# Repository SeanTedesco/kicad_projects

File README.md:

# kicad_projects
Small projects to become more familiar with PCB design and working with KiCad.

## STM-RF

## TRAFFIC LIGHT

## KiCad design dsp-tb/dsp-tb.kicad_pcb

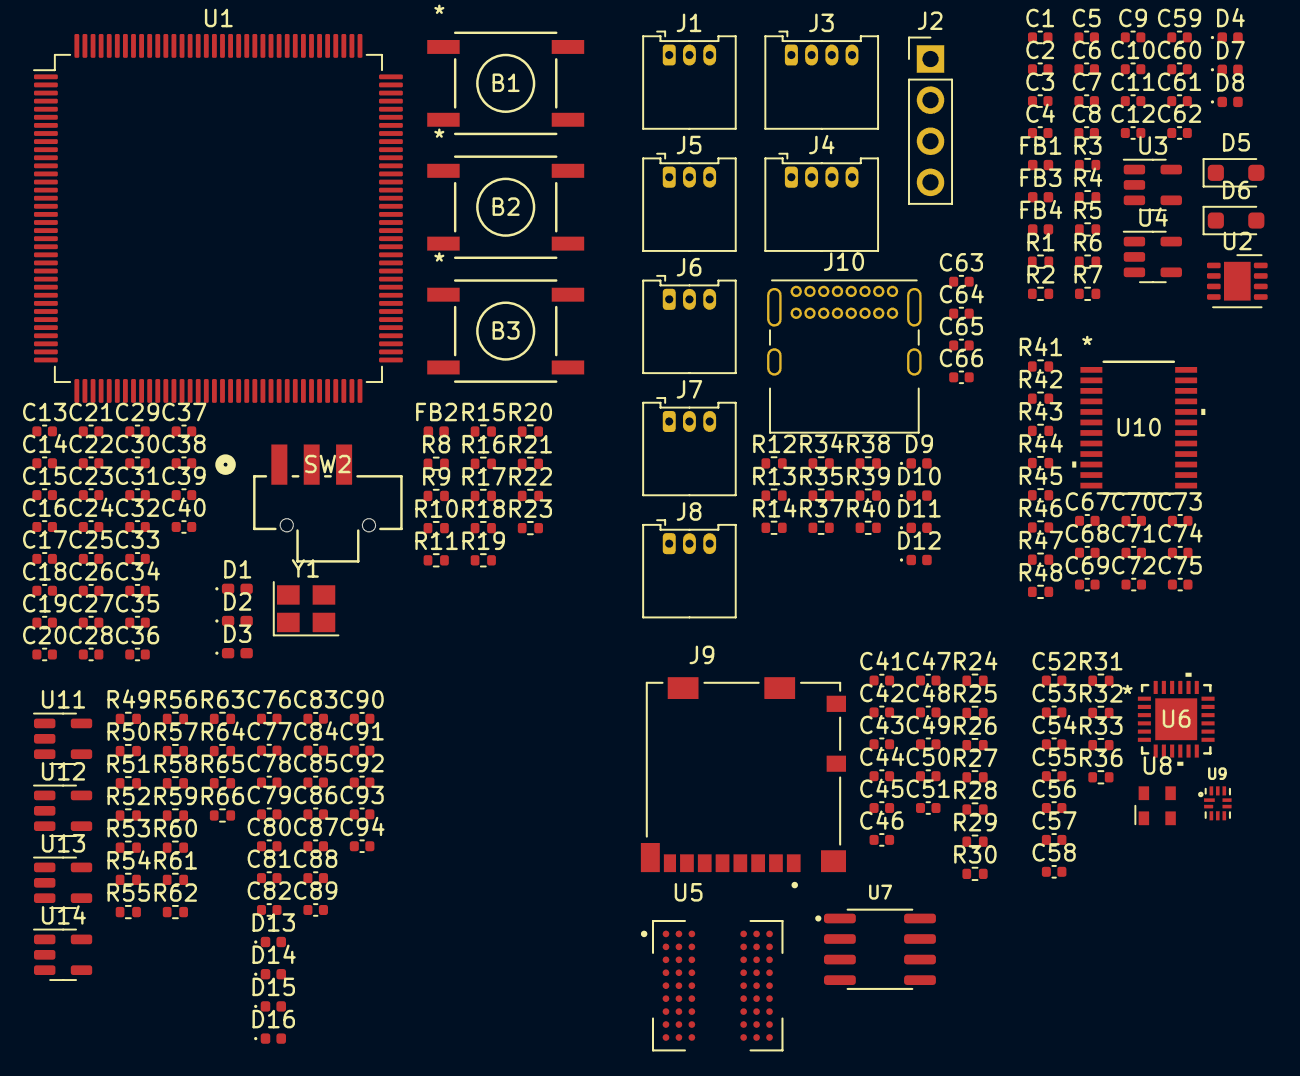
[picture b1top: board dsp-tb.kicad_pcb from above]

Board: 2 copper layers, 209 parts (0 on the bottom side), 168 nets, no tracks yet.

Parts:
B1, B2, B3: SW_MEC_5E; PTS645SL43SMTR92LFS_CNK
C1, C2, C3, C4, C5, C6, C7, C8, C13, C14, C32, C41, C45, C50, C51, C52, C53, C55, C68: 2u2; C_0402_1005Metric
C9, C10, C11, C12, C71, C72, C75, C86: 47u; C_0402_1005Metric
C15, C16, C17, C18, C19, C20, C21, C22, C23, C24, C25, C26, C27, C28, C29, C30, C31, C33, C34, C35, C36, C37, C38, C42, C43, C44, C46, C47, C48, C49, C54, C56, C57, C58, C59, C60, C61, C62, C67, C69, C70, C73, C74, C78, C83, C89, C93: 100n; C_0402_1005Metric
C39, C40, C63, C64, C65, C66: 10p; C_0402_1005Metric
C76, C79, C81, C84: 220p; C_0402_1005Metric
C77, C80, C82, C85, C87, C90, C91, C94: 10n; C_0402_1005Metric
C88, C92: 1n; C_0402_1005Metric
D1: RED; LED_0402_1005Metric_Pad0.77x0.64mm_HandSolder
D2: YLW; LED_0402_1005Metric_Pad0.77x0.64mm_HandSolder
D3: BLU; LED_0402_1005Metric_Pad0.77x0.64mm_HandSolder
D4, D7, D8, D9, D10, D11, D12, D13, D14, D15, D16: CG0402MLU-12G; D_0402_1005Metric
D5, D6: BAT165A; D_SOD-323_HandSoldering
FB1, FB3, FB4: 120R@100MHz; L_0402_1005Metric
FB2: 120R@100Mhz; L_0402_1005Metric
J1, J5, J6, J7, J8: Conn_01x03; Molex_PicoBlade_53048-0310_1x03_P1.25mm_Horizontal
J2: Conn_01x04; PinHeader_1x04_P2.54mm_Vertical
J3, J4: Conn_01x04; Molex_PicoBlade_53048-0410_1x04_P1.25mm_Horizontal
J9: 104031-0811; MOLEX_104031-0811
J10: USB_C_Receptacle_USB2.0; USB_C_Receptacle_GCT_USB4085
R1, R22: 0; R_0402_1005Metric
R2: DNP; R_0402_1005Metric
R3, R5, R24, R25, R26, R27, R28, R29, R30, R48: 47k; R_0402_1005Metric
R4: 15k; R_0402_1005Metric
R6: 91k; R_0402_1005Metric
R7: 10; R_0402_1005Metric
R8, R44, R45, R46, R47, R65, R66: 10k; R_0402_1005Metric
R9, R10, R11: 330; R_0402_1005Metric
R12, R13, R14, R17, R18, R19, R20, R21, R23, R31, R37, R38, R39, R40, R41: 33; R_0402_1005Metric
R15, R16: 4k7; R_0402_1005Metric
R32, R34, R35, R36: 5k1; R_0402_1005Metric
R33: 8k06; R_0402_1005Metric
R42, R43: 2k2; R_0402_1005Metric
R49, R53, R61, R64: 100R; R_0402_1005Metric
R50, R51, R54, R55, R59, R62: 1M; R_0402_1005Metric
R52, R56, R57, R58, R60, R63: 1k; R_0402_1005Metric
SW2: SW_SPDT; CSS-1210TB_NDC
U1: STM32H723ZGTx; LQFP-144_20x20mm_P0.5mm
U2: TLV76733QWDRBxQ1; VSON-8-1EP_3x3mm_P0.65mm_EP1.65x2.4mm
U3, U4: NCP718BSNADJT1G; SOT-23-5
U5: IS42S16800F-7BLI; BGA54C80P9X9_800X800X120
U6: USB3318C-CP-TR; QFN24_4X4MC_MCH
U7: IS25LP080D-JNLE; SOIC127P600X88-8N
U8: ECS-2520MV-130-BN-TR; Oscillator_SMD_Abracon_ASDMB-4Pin_2.5x2.0mm
U9: FSUSB42UMX; IC_FSUSB42UMX
U10: CS4270-CZZ; codec-cs4270
U11, U12, U13, U14: TLV9301xDBV; SOT-23-5
Y1: 403C11A24M; Crystal_SMD_3225-4Pin_3.2x2.5mm

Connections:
3V3_ADC: C61.1, D8.1 (K), FB4.1, J5.1, J6.1, J7.1, J8.1
+1V8: C6.1, C56.1, R5.1, U4.5 (OUT), U6.21 (VDD1.8)
+3.3VA: C34.1, C35.1, FB2.2, U1.32 (VREF+), U1.33 (VDDA)
+3V3: C2.1, C5.1, C15.1, C16.1, C17.1, C18.1, C19.1, C20.1, C21.1, C22.1, C23.1, C24.1, C25.1, C26.1, C27.1, C28.1, C29.1, C30.1, C31.1, C32.1, C33.1, C41.1, C42.1, C43.1, C44.1, C45.1, C46.1, C47.1, C48.1, C49.1, C50.1, C51.1, C52.1, C54.1, C57.1, C58.1, C62.1, C67.1, C68.1, C69.1, FB2.1, FB4.2, J9.4 (VDD), R1.1, R15.1, R16.1, R22.2, R24.1, R25.1, R26.1, R27.1, R28.1, R29.1, R30.1, R42.2, R43.2, SW2.3 (C), U1.6 (VBAT), U1.17 (VDD), U1.30 (VDD), U1.39 (VDD), U1.52 (VDD), U1.62 (VDD), U1.72 (VDD), U1.84 (VDD), U1.95 (VDD33USB), U1.108 (VDD), U1.121 (VDD), U1.131 (VDD), U1.144 (VDD), U2.1 (OUT), U4.1 (IN), U4.3 (EN), U5.A7 (VDDQ), U5.A9 (VDD), U5.B3 (VDDQ), U5.C7 (VDDQ), U5.D3 (VDDQ), U5.E7 (VDD), U5.J9 (VDD), U6.3 (VBAT), U6.17 (VDDIO), U7.8 (VCC), U8.1 (Standby), U8.4 (VDD), U9.9 (VCC), U10.5 (VD), U10.8 (VLC)
+5V: C4.1, R3.1, R7.1, U3.5 (OUT)
+5VA: C9.1, C10.1, C11.1, C12.1, C74.1, C75.1, C78.1, C83.1, C89.1, C93.1, R7.2, R57.1, U10.19 (VA), U11.5 (V+), U12.5 (V+), U13.5 (V+), U14.5 (V+)
/MCU/FMC_SDCLK: R23.1, U1.93 (PG8)
/MCU/MCU_BOOT0: R8.2, U1.138 (BOOT0)
/MCU/MCU_PDR_ON: R22.1, U1.143 (PDR_ON)
/MCU/QSPI_CLK_R: R21.1, U1.22 (PF10)
/MCU/SAI1_FS_A: R18.1, U1.3 (PE4)
/MCU/SAI1_MCLK_A: R17.1, U1.1 (PE2)
/MCU/SAI1_SCK_A: R19.1, U1.4 (PE5)
/MCU/SAI1_SD_A: R20.1, U1.5 (PE6)
ADC_IN14: C66.1, R40.1, U1.36 (PA2)
ADC_IN16: C65.1, R39.1, U1.34 (PA0)
ADC_IN17: C64.1, R38.1, U1.35 (PA1)
ADC_IN18: C63.1, R37.1, U1.40 (PA4)
AUDIO_IN_L: D13.1 (K), J3.1, R49.2
AUDIO_IN_R: D14.1 (K), J3.3, R53.2
AUDIO_OUT_L: C90.2, D15.1 (K), J4.1, R65.1
AUDIO_OUT_R: C94.2, D16.1 (K), J4.3, R66.1
CODEC_IN_L: C80.2, U10.15 (AINA)
CODEC_IN_R: C85.2, U10.16 (AINB)
CODEC_NRST: R47.2, U1.7 (PC13), U10.14 (*RST)
CODEC_OUT_L: C87.1, U10.22 (AOUTA)
CODEC_OUT_R: C91.1, U10.23 (AOUTB)
GND: B1.1, B1.2, B2.1, B2.2, B3.1, B3.2, C1.2, C2.2, C3.2, C4.2, C5.2, C6.2, C7.2, C8.2, C9.2, C10.2, C11.2, C12.2, C13.2, C14.2, C15.2, C16.2, C17.2, C18.2, C19.2, C20.2, C21.2, C22.2, C23.2, C24.2, C25.2, C26.2, C27.2, C28.2, C29.2, C30.2, C31.2, C32.2, C33.2, C34.2, C35.2, C36.1, C37.1, C38.1, C39.1, C40.1, C41.2, C42.2, C43.2, C44.2, C51.2, C52.2, C53.2, C54.2, C55.2, C56.2, C57.2, C58.2, C59.2, C60.2, C61.2, C62.2, C63.2, C64.2, C65.2, C66.2, C67.2, C68.2, C69.2, C70.2, C71.2, C72.2, C73.2, C74.2, C75.2, C76.2, C78.2, C79.2, C81.2, C83.2, C84.2, C86.2, C88.2, C89.2, C92.2, C93.2, D4.2 (A), D7.2 (A), D8.2 (A), D9.2 (A), D10.2 (A), D11.2 (A), D12.2 (A), D13.2 (A), D14.2 (A), D15.2 (A), D16.2 (A), J1.1, J1.2, J2.4, J3.2, J3.4, J4.2, J4.4, J5.3, J6.3, J7.3, J8.3, J9.6 (VSS), J9.G1 (GND), J9.G2 (GND), J9.G3 (GND), J9.G4 (GND), J10.A1 (GND), J10.A12 (GND), J10.B1 (GND), J10.B12 (GND), R2.2, R4.2, R6.2, R9.2, R10.2, R11.2, R33.2, R34.2, R35.2, R36.2, R44.1, R45.1, R46.1, R47.1, R48.1, R50.2, R54.2, R58.2, R65.2, R66.2, SW2.1 (A), U1.16 (VSS), U1.31 (VSSA), U1.38 (VSS), U1.51 (VSS), U1.61 (VSS), U1.83 (VSS), U1.94 (VSS), U1.107 (VSS), U1.120 (VSS), U1.130 (VSS), U2.4 (GND), U2.6 (GND), U2.9 (PAD), U3.2 (GND), U4.2 (GND), U5.A1 (VSS), U5.A3 (VSSQ), U5.B7 (VSSQ), U5.C3 (VSSQ), U5.D7 (VSSQ), U5.E3 (VSS), U5.J1 (VSS), U6.25 (EPAD), U7.4 (GND), U8.2 (GND), U9.3 (GND), U9.8 (~OE), U10.6 (DGND), U10.20 (AGND), U11.2 (V-), U12.2 (V-), U13.2 (V-), U14.2 (V-), Y1.2, Y1.4
I2C4_SCL: R43.1, U1.81 (PD12), U10.10 (M0)
I2C4_SDA: R42.1, U1.82 (PD13), U10.9 (M1)
I2S_BCLK: R19.2, U10.4 (SCLK)
I2S_DAC_IN: R20.2, U10.1 (SDIN)
I2S_MCLK: R17.2, U10.3 (MCLK)
I2S_WCLK: R18.2, U10.2 (LRCK)
MCU_BTN1: B3.3 (K), B3.4 (A), C37.2, R15.2
MCU_BTN2: B2.3 (K), B2.4 (A), C38.2, R16.2
MCU_SWCLK: R12.1, U1.109 (PA14(JTCK)
MCU_SWDIO: R13.1, U1.105 (PA13(JTMS)
MCU_SWO: R14.1, U1.133 (PB3(JTDO)
unnamed: B1.3 (K), B1.4 (A), C36.2, U1.25 (NRST)
unnamed: C13.1, U1.71 (VCAP)
unnamed: C14.1, U1.106 (VCAP)
unnamed: C45.2, C46.2, C47.2, C48.2
unnamed: C49.2, C50.2
unnamed: C76.1, C77.1, R49.1, R50.1
unnamed: C79.1, C80.1, R52.1
unnamed: C81.1, C82.1, R53.1, R54.1
unnamed: C84.1, C85.1, R56.1
unnamed: C87.2, R59.2, R60.2
unnamed: C90.1, R61.1
unnamed: C91.2, R62.2, R63.2
unnamed: C94.1, R64.1
unnamed: D1.1 (K), R9.1
unnamed: D2.1 (K), R10.1
unnamed: D3.1 (K), R11.1
unnamed: C7.1, D5.1 (K), FB1.1
unnamed: C60.1, D6.2 (A), FB3.2
unnamed: C1.1, C3.1, C8.1, D6.1 (K), FB1.2, U2.5 (EN), U2.8 (IN), U3.1 (IN), U3.3 (EN)
unnamed: D9.1 (K), J5.2, R37.2
unnamed: D10.1 (K), J6.2, R38.2
unnamed: D11.1 (K), J7.2, R39.2
unnamed: D12.1 (K), J8.2, R40.2
unnamed: J2.1, R12.2
unnamed: J2.2, R13.2
unnamed: J2.3, R14.2
unnamed: J10.A5 (CC1), R35.1
unnamed: J10.B5 (CC2), R34.1
unnamed: R8.1, SW2.2 (B)
unnamed: C39.2, U1.23 (PH0), Y1.1
unnamed: C40.2, U1.24 (PH1), Y1.3
unnamed: R1.2, R2.1, U2.3 (SNS)
unnamed: R3.2, R4.1, U3.4 (ADJ)
unnamed: R5.2, R6.1, U4.4 (ADJ)
unnamed: R33.1, U6.24 (RBIAS)
unnamed: R31.1, U6.23 (REFCLK)
unnamed: R32.2, U6.2 (VBUS)
unnamed: C55.1, U6.4 (VDD3.3)
unnamed: R31.2, U8.3 (Out)
unnamed: C72.1, C73.1, U10.18 (FILT+)
unnamed: R44.2, U10.11 (I2S/*LJ)
unnamed: R45.2, U10.12 (MDIV1)
unnamed: R46.2, U10.13 (MDIV2)
unnamed: R41.1, R48.2, U10.7 (SDOUT)
unnamed: C70.1, C71.1, U10.17 (VQ)
unnamed: C77.2, R51.2, U11.3 (+)
unnamed: R52.2, U11.1, U11.4 (-)
unnamed: C82.2, R55.2, U12.3 (+)
unnamed: R56.2, U12.1, U12.4 (-)
unnamed: C88.1, R60.1, U13.3 (+)
unnamed: R61.2, U13.1, U13.4 (-)
unnamed: C92.1, R63.1, U14.3 (+)
unnamed: R64.2, U14.1, U14.4 (-)
QSPI_CLK: R21.2, U7.6 (SCK)
QSPI_IO0: U1.20 (PF8), U7.2 (SO(IO1))
QSPI_IO1: U1.21 (PF9), U7.5 (SI(IO0))
QSPI_IO2: U1.19 (PF7), U7.3 (WP#(IO2))
QSPI_IO3: U1.18 (PF6), U7.7 (HOLD/RESET)
QSPI_NCS: R30.2, U1.91 (PG6), U7.1 (CE#)
RAM_A0: U1.10 (PF0), U5.H7 (A0)
RAM_A1: U1.11 (PF1), U5.H8 (A1)
RAM_A2: U1.12 (PF2), U5.J8 (A2)
RAM_A3: U1.13 (PF3), U5.J7 (A3)
RAM_A4: U1.14 (PF4), U5.J3 (A4)
RAM_A5: U1.15 (PF5), U5.J2 (A5)
RAM_A6: U1.50 (PF12), U5.H3 (A6)
RAM_A7: U1.53 (PF13), U5.H2 (A7)
RAM_A8: U1.54 (PF14), U5.H1 (A8)
RAM_A9: U1.55 (PF15), U5.G3 (A9)
RAM_A10: U1.56 (PG0), U5.H9 (A10)
RAM_A11: U1.57 (PG1), U5.G2 (A11)
RAM_BA0: U1.89 (PG4), U5.G7 (BA0)
RAM_BA1: U1.90 (PG5), U5.G8 (BA1)
RAM_CKE: U1.45 (PC5), U5.F3 (CKE)
RAM_CLK: R23.2, U5.F2 (CLK)
RAM_D0: U1.85 (PD14), U5.A8 (DQ0)
RAM_D1: U1.86 (PD15), U5.B9 (DQ1)
RAM_D2: U1.114 (PD0), U5.B8 (DQ2)
RAM_D3: U1.115 (PD1), U5.C9 (DQ3)
RAM_D4: U1.58 (PE7), U5.C8 (DQ4)
RAM_D5: U1.59 (PE8), U5.D9 (DQ5)
RAM_D6: U1.60 (PE9), U5.D8 (DQ6)
RAM_D7: U1.63 (PE10), U5.E9 (DQ7)
RAM_D8: U1.64 (PE11), U5.E1 (DQ8)
RAM_D9: U1.65 (PE12), U5.D2 (DQ9)
RAM_D10: U1.66 (PE13), U5.D1 (DQ10)
RAM_D11: U1.67 (PE14), U5.C2 (DQ11)
RAM_D12: U1.68 (PE15), U5.C1 (DQ12)
RAM_D13: U1.77 (PD8), U5.B2 (DQ13)
RAM_D14: U1.78 (PD9), U5.B1 (DQ14)
RAM_D15: U1.79 (PD10), U5.A2 (DQ15)
RAM_DMH: U1.142 (PE1), U5.F1 (DQMH)
RAM_DML: U1.141 (PE0), U5.E8 (DQML)
RAM_NCAS: U1.132 (PG15), U5.F7 (*CAS)
RAM_NCS: U1.44 (PC4), U5.G9 (*CS)
RAM_NRAS: U1.49 (PF11), U5.F8 (*RAS)
RAM_NWE: U1.43 (PA7), U5.F9 (*WE)
SAI1_SD_B: R41.2, U1.2 (PE3)
SD_CLK: J9.5 (CLK), U1.122 (PD6)
SD_CMD: J9.3 (CMD), R29.2, U1.123 (PD7)
SD_D0: J9.7 (DAT0), R24.2, U1.124 (PG9)
SD_D1: J9.8 (DAT1), R25.2, U1.125 (PG10)
SD_D2: J9.1 (DAT2), R26.2, U1.126 (PG11)
SD_D3: J9.2 (CD/DAT3), R27.2, U1.127 (PG12)
SD_DET: J9.9 (SW-1), R28.2, U1.128 (PG13)
ULPI_CLK: U1.41 (PA5), U6.12 (CLKOUT)
ULPI_D0: U1.37 (PA3), U6.16 (DATA0)
ULPI_D1: U1.46 (PB0), U6.15 (DATA1)
ULPI_D2: U1.47 (PB1), U6.14 (DATA2)
ULPI_D3: U1.69 (PB10), U6.13 (DATA3)
ULPI_D4: U1.70 (PB11), U6.11 (DATA4)
ULPI_D5: U1.73 (PB12), U6.10 (DATA5)
ULPI_D6: U1.74 (PB13), U6.9 (DATA6)
ULPI_D7: U1.135 (PB5), U6.8 (DATA7)
ULPI_DIR: U1.28 (PC2_C), U6.19 (DIR)
ULPI_NXT: U1.29 (PC3_C), U6.18 (NXT)
ULPI_STP: U1.26 (PC0), U6.20 (STP)
USB_D_N: J10.A7 (D-), J10.B7 (D-), U9.2 (D-)
USB_D_P: J10.A6 (D+), J10.B6 (D+), U9.1 (D+)
USB_FS_D_N: U1.103 (PA11), U9.6 (HSD2-)
USB_FS_D_P: U1.104 (PA12), U9.7 (HSD2+)
USB_HS_D_N: U6.5 (DM), U9.4 (HSD1-)
USB_HS_D_P: U6.6 (DP), U9.5 (HSD1+)
USB_NRST: U1.129 (PG14), U6.22 (RESETB)
USB_SW: R36.1, U1.102 (PA10), U9.10 (SEL)
VBUS: C59.1, D7.1 (K), FB3.1, J10.A4 (VBUS), J10.A9 (VBUS), J10.B4 (VBUS), J10.B9 (VBUS)
VCC: D4.1 (K), D5.2 (A), J1.3
VCOM: C86.1, R51.1, R55.1, R57.2, R58.1, R59.1, R62.1
VUSB_FILT: C53.1, R32.1

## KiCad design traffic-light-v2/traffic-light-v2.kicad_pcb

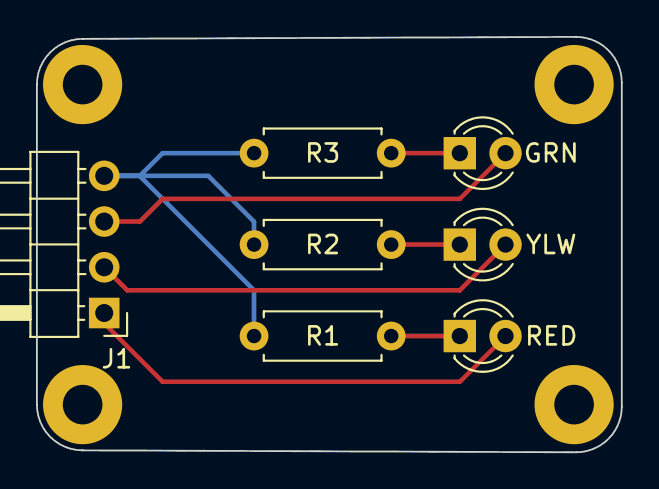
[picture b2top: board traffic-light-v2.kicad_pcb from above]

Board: 2 copper layers, 32.5 x 23.1 mm, 11 parts (0 on the bottom side), 7 nets.

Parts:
GRN: GRN; LED_D3.0mm
H1, H2, H3, H4: MountingHole; MountingHole_2.2mm_M2_Pad
J1: Conn_01x04; PinHeader_1x04_P2.54mm_Horizontal
R1, R2, R3: 330; R_Axial_DIN0207_L6.3mm_D2.5mm_P7.62mm_Horizontal
RED: RED; LED_D3.0mm
YLW: YLW; LED_D3.0mm

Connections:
GND: J1.4, R1.2, R2.2, R3.2
LED_GRN: GRN.2 (A), J1.3
LED_RED: J1.1, RED.2 (A)
LED_YLW: J1.2, YLW.2 (A)
unnamed: R1.1, RED.1 (K)
unnamed: R2.1, YLW.1 (K)
unnamed: GRN.1 (K), R3.1

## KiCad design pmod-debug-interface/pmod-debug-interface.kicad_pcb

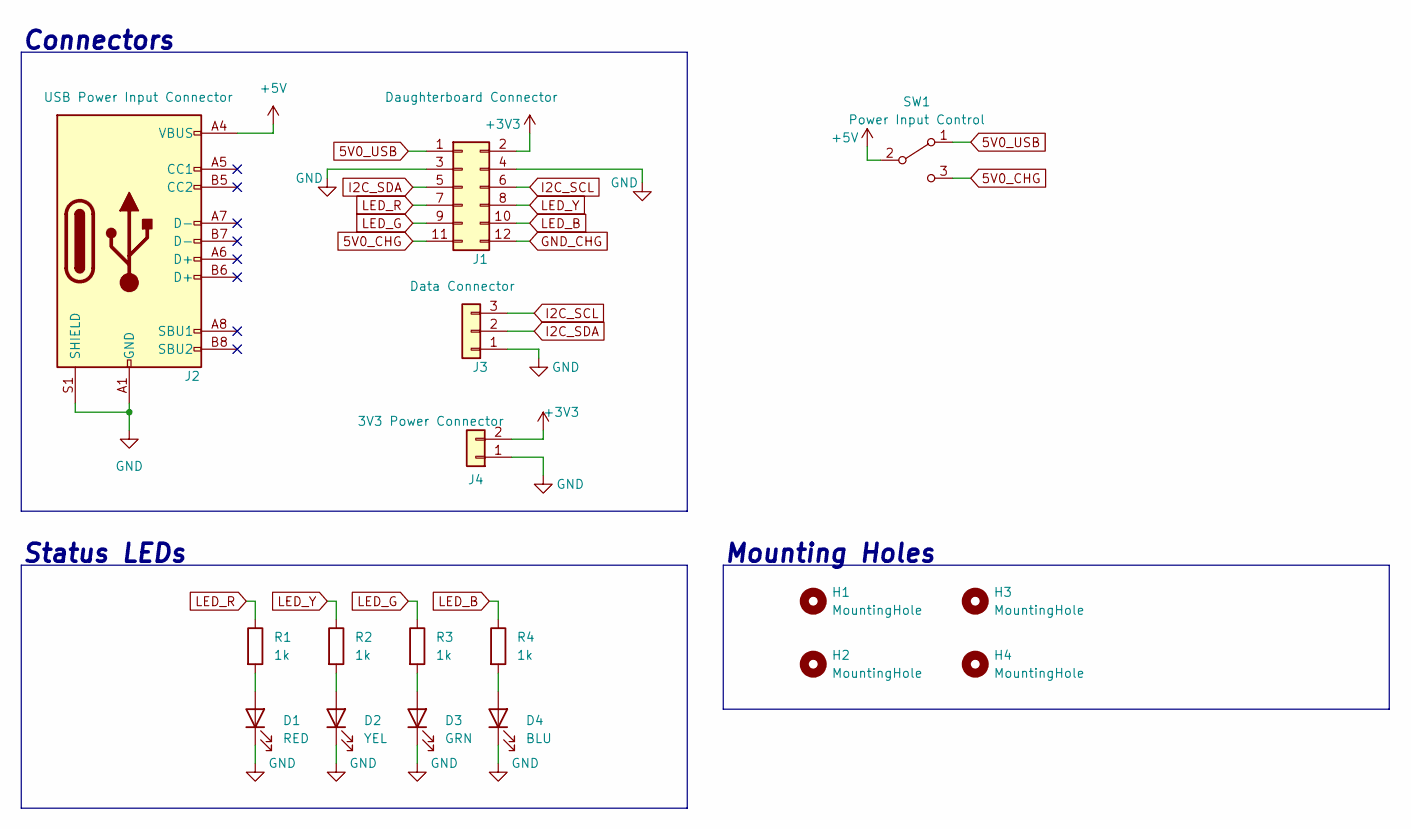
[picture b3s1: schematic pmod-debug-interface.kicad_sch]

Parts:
D1: RED; LED_D3.0mm
D2: YEL; LED_D3.0mm
D3: GRN; LED_D3.0mm
D4: BLU; LED_D3.0mm
H1, H2, H3, H4: MountingHole; MountingHole_2.2mm_M2_Pad
J1: Daughterboard Connector; PinHeader_2x06_P2.54mm_Horizontal
J2: USB Power Input Connector; USB_C_Receptacle_GCT_USB4085
J3: Data Connector; PinHeader_1x03_P2.54mm_Vertical
J4: 3V3 Power Connector; PinSocket_1x02_P2.54mm_Vertical
R1, R2, R3, R4: 1k; R_Axial_DIN0207_L6.3mm_D2.5mm_P7.62mm_Horizontal
SW1: Power Input Control; L102021MS02Q

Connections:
5V0_CHG: J1.11, SW1.3 (C)
5V0_USB: J1.1, SW1.1 (A)
+3V3: J1.2, J4.2
+5V: J2.A4 (VBUS), J2.A9 (VBUS), J2.B4 (VBUS), J2.B9 (VBUS), SW1.2 (B)
GND: D1.1 (K), D2.1 (K), D3.1 (K), D4.1 (K), J1.3, J1.4, J2.A1 (GND), J2.A12 (GND), J2.B1 (GND), J2.B12 (GND), J2.S1 (SHIELD), J3.1, J4.1
GND_CHG: J1.12
I2C_SCL: J1.6, J3.3
I2C_SDA: J1.5, J3.2
LED_B: J1.10, R4.1
LED_G: J1.9, R3.1
LED_R: J1.7, R1.1
LED_Y: J1.8, R2.1
unnamed: D1.2 (A), R1.2
unnamed: D2.2 (A), R2.2
unnamed: D3.2 (A), R3.2
unnamed: D4.2 (A), R4.2

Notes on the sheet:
Connectors
Mounting Holes
Status LEDs

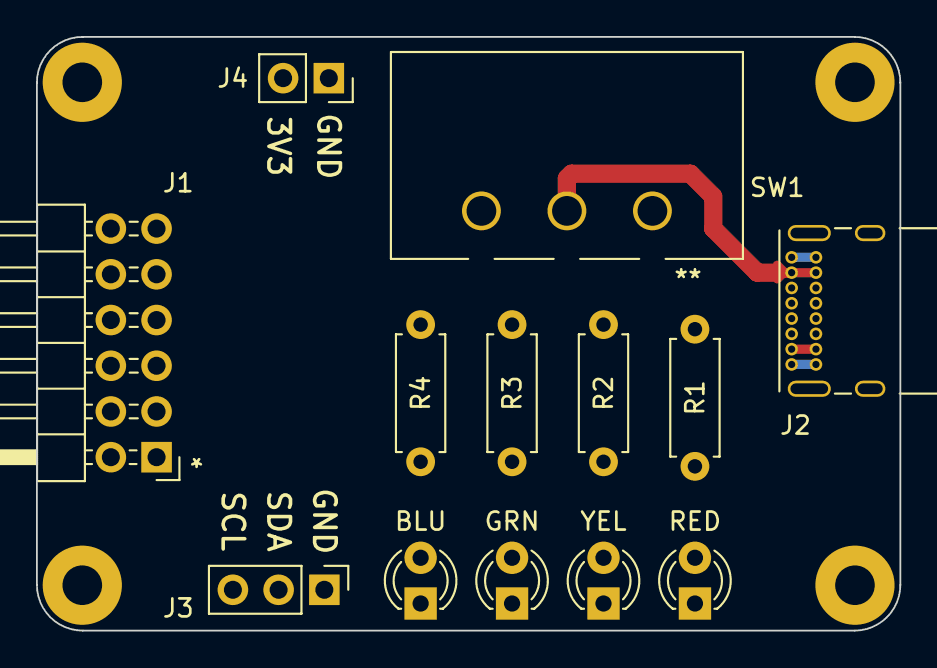
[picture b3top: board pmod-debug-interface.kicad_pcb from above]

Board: 2 copper layers, 48.0 x 33.0 mm, 17 parts (0 on the bottom side), 15 nets.

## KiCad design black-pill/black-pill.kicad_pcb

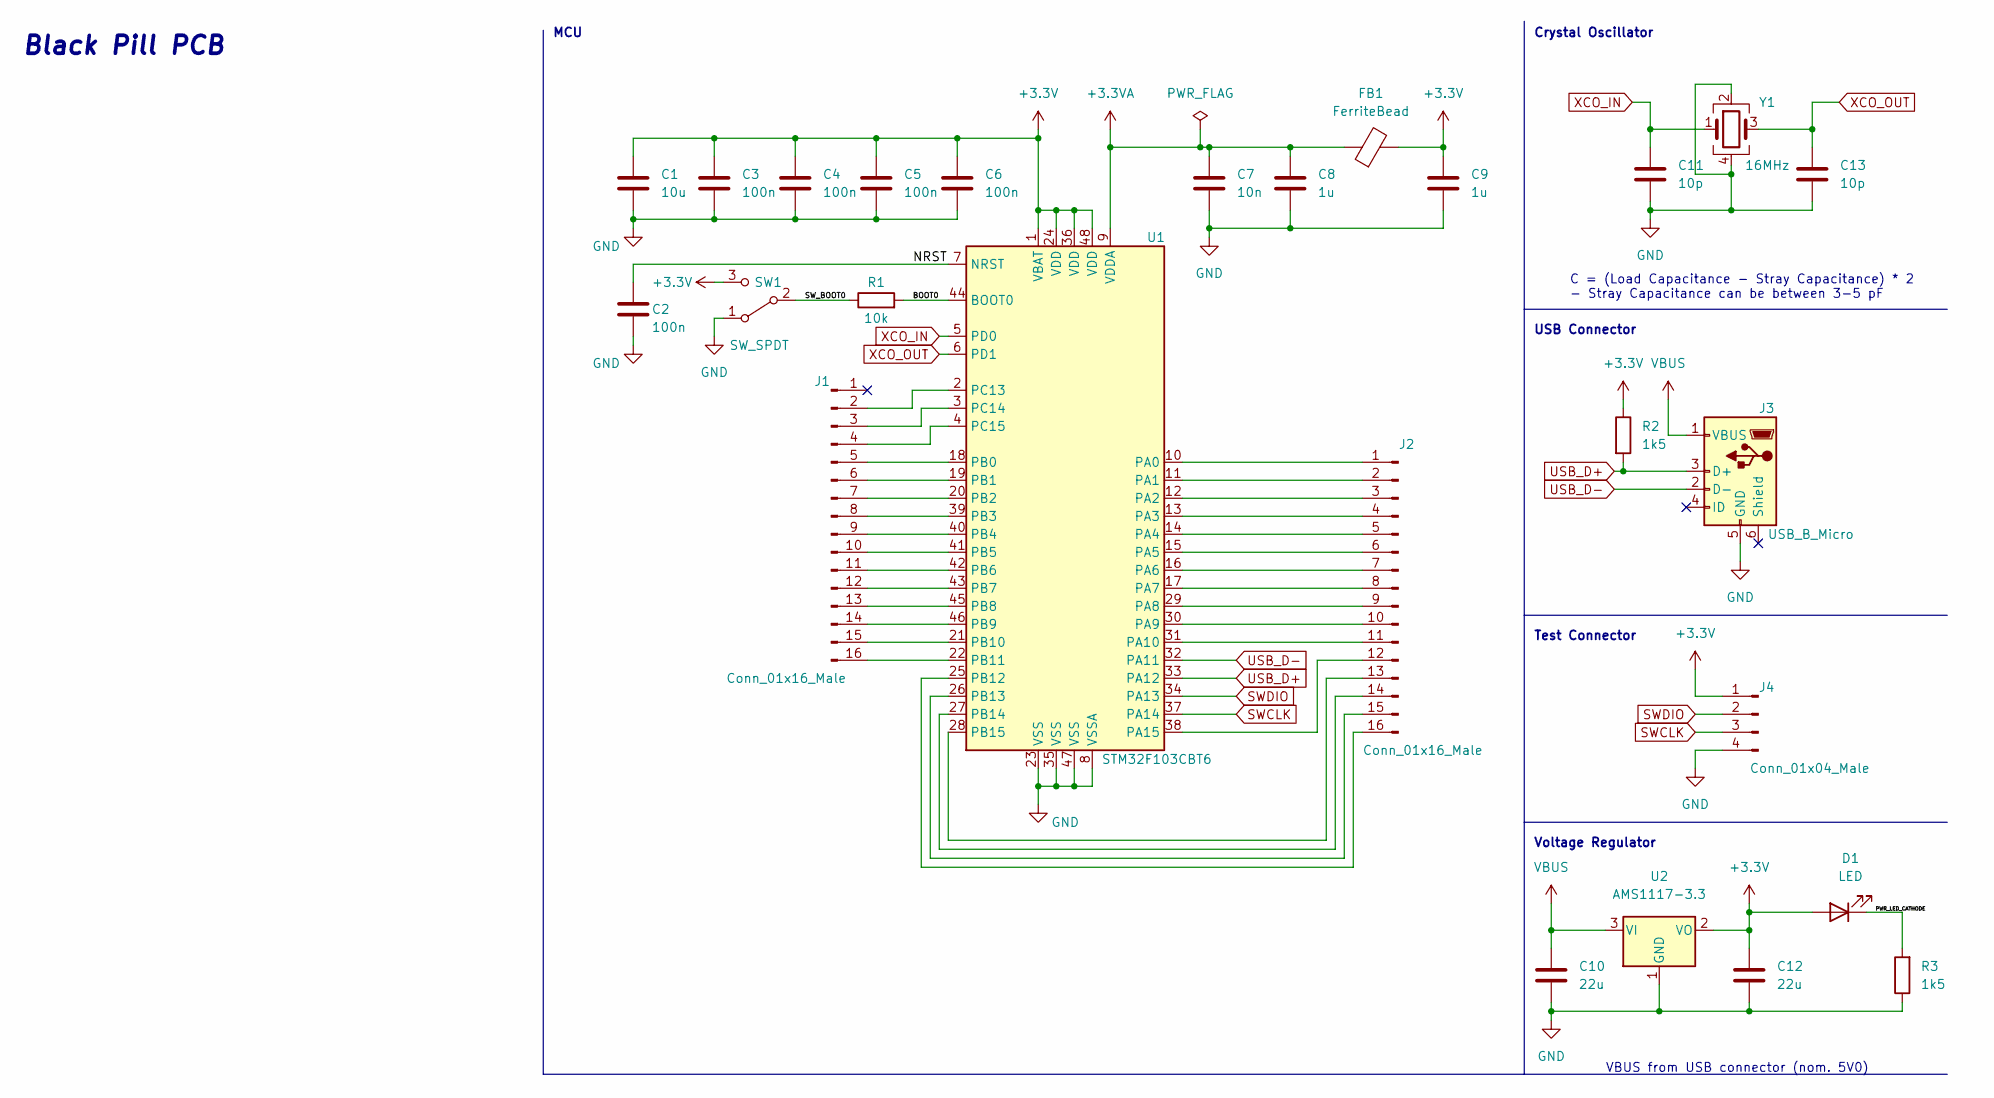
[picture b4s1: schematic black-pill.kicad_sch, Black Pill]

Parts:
C1: 10u; C_0603_1608Metric
C2, C3, C4, C5, C6: 100n; C_0402_1005Metric
C7: 10n; C_0402_1005Metric
C8, C9: 1u; C_0402_1005Metric
C10, C12: 22u; C_0805_2012Metric
C11, C13: 10p; C_0402_1005Metric
D1: LED; LED_0603_1608Metric
FB1: FerriteBead; L_0603_1608Metric
J1, J2: Conn_01x16_Male; PinHeader_1x16_P2.54mm_Vertical
J3: USB_B_Micro; USB_Micro-B_Wuerth_629105150521
J4: Conn_01x04_Male; PinHeader_1x04_P2.54mm_Vertical
R1: 10k; R_0402_1005Metric
R2, R3: 1k5; R_0402_1005Metric
SW1: SW_SPDT; SW_SPDT_PCM12
U1: STM32F103CBT6; LQFP-48_7x7mm_P0.5mm
U2: AMS1117-3.3; SOT-223-3_TabPin2
Y1: 16MHz; Crystal_SMD_3225-4Pin_3.2x2.5mm

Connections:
+3.3V: C1.1, C3.1, C4.1, C5.1, C6.1, C9.1, C12.1, D1.2 (A), FB1.2, J4.1, R2.1, SW1.3 (C), U1.1 (VBAT), U1.24 (VDD), U1.36 (VDD), U1.48 (VDD), U2.2 (VO)
+3.3VA: C7.1, C8.1, FB1.1, U1.9 (VDDA)
/BOOT0: R1.2, U1.44 (BOOT0)
/NRST: C2.1, U1.7 (NRST)
/PWR_LED_CATHODE: D1.1 (K), R3.2
/SW_BOOT0: R1.1, SW1.2 (B)
GND: C1.2, C2.2, C3.2, C4.2, C5.2, C6.2, C7.2, C8.2, C9.2, C10.2, C11.2, C12.2, C13.2, J3.5 (GND), J4.4, R3.1, SW1.1 (A), U1.8 (VSSA), U1.23 (VSS), U1.35 (VSS), U1.47 (VSS), U2.1 (GND), Y1.2, Y1.4
unnamed: J1.2, U1.2 (PC13)
unnamed: J1.3, U1.3 (PC14)
unnamed: J1.4, U1.4 (PC15)
unnamed: J1.5, U1.18 (PB0)
unnamed: J1.6, U1.19 (PB1)
unnamed: J1.7, U1.20 (PB2)
unnamed: J1.8, U1.39 (PB3)
unnamed: J1.9, U1.40 (PB4)
unnamed: J1.10, U1.41 (PB5)
unnamed: J1.11, U1.42 (PB6)
unnamed: J1.12, U1.43 (PB7)
unnamed: J1.13, U1.45 (PB8)
unnamed: J1.14, U1.46 (PB9)
unnamed: J1.15, U1.21 (PB10)
unnamed: J1.16, U1.22 (PB11)
unnamed: J2.1, U1.10 (PA0)
unnamed: J2.2, U1.11 (PA1)
unnamed: J2.3, U1.12 (PA2)
unnamed: J2.4, U1.13 (PA3)
unnamed: J2.5, U1.14 (PA4)
unnamed: J2.6, U1.15 (PA5)
unnamed: J2.7, U1.16 (PA6)
unnamed: J2.8, U1.17 (PA7)
unnamed: J2.9, U1.29 (PA8)
unnamed: J2.10, U1.30 (PA9)
unnamed: J2.11, U1.31 (PA10)
unnamed: J2.12, U1.38 (PA15)
unnamed: J2.13, U1.28 (PB15)
unnamed: J2.14, U1.27 (PB14)
unnamed: J2.15, U1.26 (PB13)
unnamed: J2.16, U1.25 (PB12)
SWCLK: J4.3, U1.37 (PA14)
SWDIO: J4.2, U1.34 (PA13)
USB_D+: J3.3 (D+), R2.2, U1.33 (PA12)
USB_D-: J3.2 (D-), U1.32 (PA11)
VBUS: C10.1, J3.1 (VBUS), U2.3 (VI)
XCO_IN: C11.1, U1.5 (PD0), Y1.1
XCO_OUT: C13.1, U1.6 (PD1), Y1.3

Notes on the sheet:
Test Connector
Crystal Oscillator
MCU
USB Connector
Voltage Regulator
C = (Load Capacitance - Stray Capacitance) * 2 - Stray Capacitance can be between 3-5 pF
VBUS from USB connector (nom. 5V0)
Black Pill PCB

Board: 2 copper layers, 26 parts (0 on the bottom side), 45 nets, no tracks yet.

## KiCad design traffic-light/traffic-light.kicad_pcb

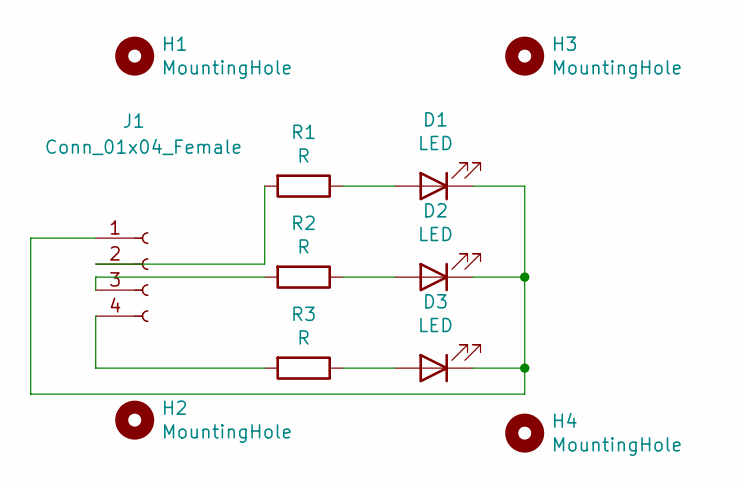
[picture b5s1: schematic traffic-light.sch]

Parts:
D1, D2, D3: LED; LED_D3.0mm
H1, H2, H3, H4: MountingHole; MountingHole_2.5mm_Pad
J1: Conn_01x04_Female; PinHeader_1x04_P2.54mm_Horizontal
R1, R2, R3: R; R_Axial_DIN0204_L3.6mm_D1.6mm_P5.08mm_Horizontal

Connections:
unnamed: D1.1 (K), D2.1 (K), D3.1 (K), J1.1
unnamed: D1.2 (A), R1.1
unnamed: D2.2 (A), R2.1
unnamed: D3.2 (A), R3.1
unnamed: J1.2, R1.2
unnamed: J1.3, R2.2
unnamed: J1.4, R3.2

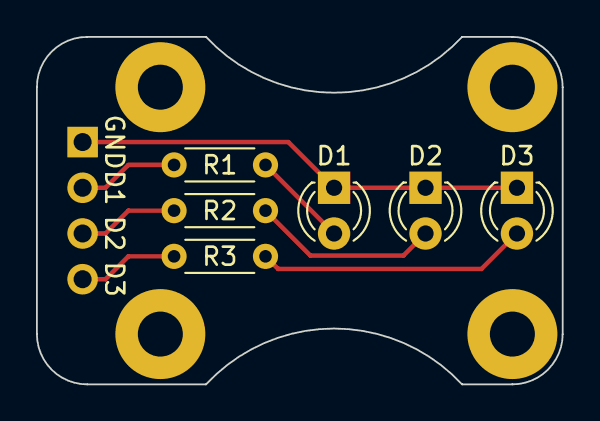
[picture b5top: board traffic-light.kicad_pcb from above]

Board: 2 copper layers, 29.2 x 19.3 mm, 11 parts (1 on the bottom side), 7 nets.

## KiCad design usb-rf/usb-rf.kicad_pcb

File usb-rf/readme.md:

# RF-USB - Universal Receiver

# Components

## STM32L432KB
- include USB interface within the chip
- ultra low power (minimal processing is required, just need an interface
 between USB and RF radio. 

## RF24L01
- 2.4 GHz Transceiver
- low cost 
- has been seen in many Arduino projects, so can use some existing librar
ies.
- SMA connector used as to not limit the antenna selection, and reducing
form factor of PCB. 

# PCB Design 

## Layers
The RF-USB uses a 4-layer PCB broken down per the following: 
- 1st Layer: Signals
- 2nd Layer: Ground
- 3rd Layer: Power (3V3)
- 4th Layer: Signal

## Design Guidelines
1. De-coupling capacitors will be placed as close to each device as possible. 
1. ESD protection device shall be as close to the USB port as possible.
1. Each ground and power pad shall have a via.

# Documentation

[nRF24L01 Datasheet](https://www.mouser.com/datasheet/2/297/nRF24L01_Product_Specification_v2_0-9199.pdf)

[STM32L432KB Datatsheet](https://www.st.com/resource/en/datasheet/stm32l432kc.pdf)

[STM32L4 Series Hardware Development](https://www.st.com/resource/en/application_note/dm00125306-getting-started-with-stm32l4-series-and-stm32l4-series-hardware-development-stmicroelectronics.pdf)

[JCLPCB Design Capabilities](https://jlcpcb.com/capabilities/Capabilities)

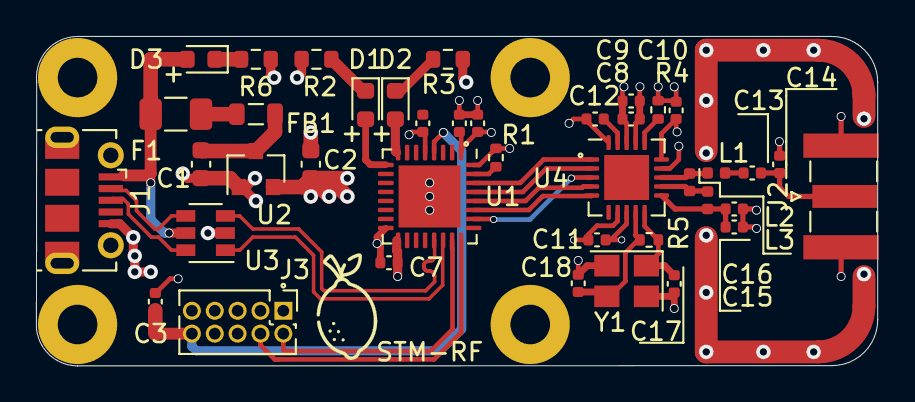
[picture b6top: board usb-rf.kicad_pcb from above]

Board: 4 copper layers, 46.7 x 18.3 mm, 44 parts (0 on the bottom side), 33 nets.

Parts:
C1, C2: 10u; C_0603_1608Metric
C3, C5, C6, C7: 100n; C_0402_1005Metric
C4: 1u; C_0402_1005Metric
C8: 10u; C_0402_1005Metric
C9, C10, C11: 10n; C_0402_1005Metric
C12: 33n; C_0402_1005Metric
C13: 1p5; C_0402_1005Metric
C14: 1p; C_0402_1005Metric
C15: 2n2; C_0402_1005Metric
C16: 4p7; C_0402_1005Metric
C17, C18: 12p; C_0402_1005Metric
D1: GR; LED_0603_1608Metric
D2: YL; LED_0603_1608Metric
D3: RD; LED_0603_1608Metric
F1: 100mA; Fuse_1206_3216Metric
FB1: 100 @ 100MHz; L_0805_2012Metric
H1, H2, H3, H4: MountingHole; MountingHole_2.2mm_M2_Pad
J1: USB_B_Micro; USB_Micro-B_Molex-105017-0001-SeanCopy
J2: SMA; SMA_Samtec_SMA-J-P-X-ST-EM1_EdgeMount-SeanCopyy
J3: ARM 10 pin; PinHeader_2x05_P1.27mm_Vertical
L1: 3n9; L_0402_1005Metric
L2: 8n2; L_0402_1005Metric
L3: 2n7; L_0402_1005Metric
R1: 10k; R_0402_1005Metric
R2, R3, R6: 2k2; R_0603_1608Metric
R4: 22k; R_0402_1005Metric
R5: 1M; R_0402_1005Metric
U1: STM32L432KBUx; QFN-32-1EP_5x5mm_P0.5mm_EP3.45x3.45mm
U2: XC6206PxxxMR; SOT-23
U3: USBLC6-2SC6; SOT-23-6
U4: nRF24L01P; QFN-20-1EP_4x4mm_P0.5mm_EP2.5x2.5mm
Y1: 16 MHz; Crystal_SMD_3225-4Pin_3.2x2.5mm

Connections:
+3V3: C2.1, C4.1, C5.1, C6.1, C7.1, C8.1, C9.1, C10.1, C11.1, J3.1, U1.1, U1.5, U1.17, U2.2, U4.7, U4.15, U4.18
+5V: D3.2, F1.1, J1.1, U3.5
GND: C1.2, C2.2, C3.2, C4.2, C5.2, C6.2, C7.2, C8.2, C9.2, C10.2, C11.2, C12.2, C14.1, C15.1, C16.1, C17.1, C18.1, J1.5, J2.2, J3.3, J3.5, J3.9, R1.2, R2.2, R3.2, R4.2, R6.1, U1.16, U1.32, U1.33, U2.1, U3.2, U4.8, U4.14, U4.17, U4.20, Y1.2, Y1.4
NRF_ANT1: L2.2, L3.1, U4.12
NRF_ANT2: L1.1, L2.1, U4.13
NRF_CE: U1.30, U4.1
NRF_IRQ: U1.25, U4.6
NRF_VDD_PA: C15.2, C16.2, L3.2, U4.11
NRF_XC1: C17.2, R5.1, U4.10, Y1.1
NRF_XC2: C18.2, R5.2, U4.9, Y1.3
NRST: C3.1, J3.10, U1.4
unnamed: C1.1, FB1.1, U2.3
unnamed: C12.1, U4.19
unnamed: C13.1, C14.2, J2.1
unnamed: C13.2, L1.2
unnamed: D1.1, R2.1
unnamed: D1.2, U1.9
unnamed: D2.1, R3.1
unnamed: D2.2, U1.8
unnamed: D3.1, R6.2
unnamed: F1.2, FB1.2
unnamed: R1.1, U1.31
unnamed: R4.1, U4.16
SPI3_CSN: U1.29, U4.2
SPI3_MISO: U1.27, U4.5
SPI3_MOSI: U1.28, U4.4
SPI3_SCK: U1.26, U4.3
SWCLK: J3.4, U1.24
SWDIO: J3.2, U1.23
USB_CONN_D+: J1.3, U3.6
USB_CONN_D-: J1.2, U3.4
USB_D+: U1.22, U3.1
USB_D-: U1.21, U3.3

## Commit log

2021-10-18 traffic-light: initial commit of schematics, footprints, and traces
2021-10-19 traffic-light: add round edges, correct pin header, add silk screen
2021-10-20 traffic-light: decrease pcb size, add gerbers, pcb is ready to order
2022-01-12 rf-usb: add schematic and footprints
2022-01-23 stm-rf: complete footprint lay out
    add: power and ground planes
2022-01-24 stm-rf: include differential routing
2022-01-27 stm-rf: add routing for spi connections
2022-01-28 stm-rf: add controlled impedance traces for RF
2022-02-05 usb-rf: continue with rf guard ring
2022-02-05 usb-rf: include step and rf guard ring
    just need manufacturing files!
2022-02-08 usb-rf: include files for fab house
2022-02-08 traffic-light: update edge cuts
2022-09-02 black pill: finish schematic and rough layout
2023-02-02 usb-rf: open project with kicad v6
2023-02-02 my-library: include more step and footprints
2023-02-02 pmod-debug-interface: begin new project
2023-09-10 lib: footprints: add footprints for future dsp-tb
2023-09-10 lib: step-files: add step files for future dsp-tb
2023-09-10 lib: symbols: add symbols for future dsp-tb
2023-09-10 dsp-tb: new test board for digital signal processing projects
2023-09-13 dsp-tb: start to include external components for mcu
2023-09-14 dsp-tb: sch: small arrangement changes
2023-09-14 dsp: boot0 and reset switches
2023-11-12 dsp-tb: finish schematic drawings
2023-11-12 lib: include necessary footprints for dsp-tb

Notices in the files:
parts and their libraries:
Copyright 2021 Accelerated Designs. All rights reserved.
